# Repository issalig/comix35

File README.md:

# comix35
This repository contains projects for Comix35

## comixino
[SW and HW](https://github.com/issalig/comix35/tree/main/comixino) for loading (and saving in the future) data/programs without the need of another computer. It is basically a mix of the HSDC and TZXDuino.

### SW
Comixino [software](https://github.com/issalig/comix35/tree/main/comixino/sw) is basically and adaption of TZXDuino for the COMIX-35. However, communication is not cassette-based but serial is used.
By pressing up/down buttons it is possible to navigate through the file system. Then, pressing PLAY will transmit the file to the COMIX-35. Please remember to type "PLOAD" in the COMIX-35 before pressing PLAY.
Recording is done similarly. First press RECORD button on comixino, then type "PSAVE" in COMIX-35. However, "record" function does not work correctly as it misses some bytes. If you can help me, please do it.

It is possible to use hardware serial or software serial (comment/uncomment #define SW_SERIAL 1)

### HW
Comixino [board](https://github.com/issalig/comix35/tree/main/comixino/hw) is made up of an Arduino Uno, OLED screen, and SD card reader and connects to the expansion port. However, it just uses 3 connections /EF4, Q and GND.
A pass-trough connection is also available allowing to experiment with the bus signals.

## Keycaps
[Keycaps](https://github.com/issalig/comix35/tree/main/keycaps) for the Comix35 clone (https://github.com/schlae/comix-35)

## Case
Modified [case](https://github.com/issalig/comix35/tree/main/case) based in https://www.thingiverse.com/thing:5405097 with hole for cartridges and left aligned keys. Suitable for printing in small/standard 3d printers.

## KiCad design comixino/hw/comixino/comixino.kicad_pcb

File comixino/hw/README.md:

# COMIXINO - COMX File Player/Recorder

## Overview
COMIXINO is an Arduino-based project that plays and records COMX files using High Speed Direct Connection (HDSC). It's designed to work with the COMX-35 computer system, allowing you to transfer programs and data between a modern SD card storage and the vintage computer.

## Hardware configuration
There are some jumpers that need to be configured.
 - J1: Powers Arduino from COMX-35. If Comixino is connected to the PC through USB it would be better not to have the jumper but it is proven to work. (Necessary)
 - J2: If connected it resets both Comixino and COMX-35 when reset button is pressed. (Recommended)
 - J11: TX. Set to HW (hardware serial) as default option. Set it to SW (software serial) if you compiled it ```#define SW_SERIAL 1 ``` (Recommended HW)
- J12: RX. Set to HW (hardware serial) as default option. Set it to SW (software serial) if you compiled it ```#define SW_SERIAL 1 ``` (Recommended HW)
 - J8: Original connector from HSDC board that plugs to an RS232-USB converter.
 - J7: Exposed pins for software serial TX/RX (not necessary)

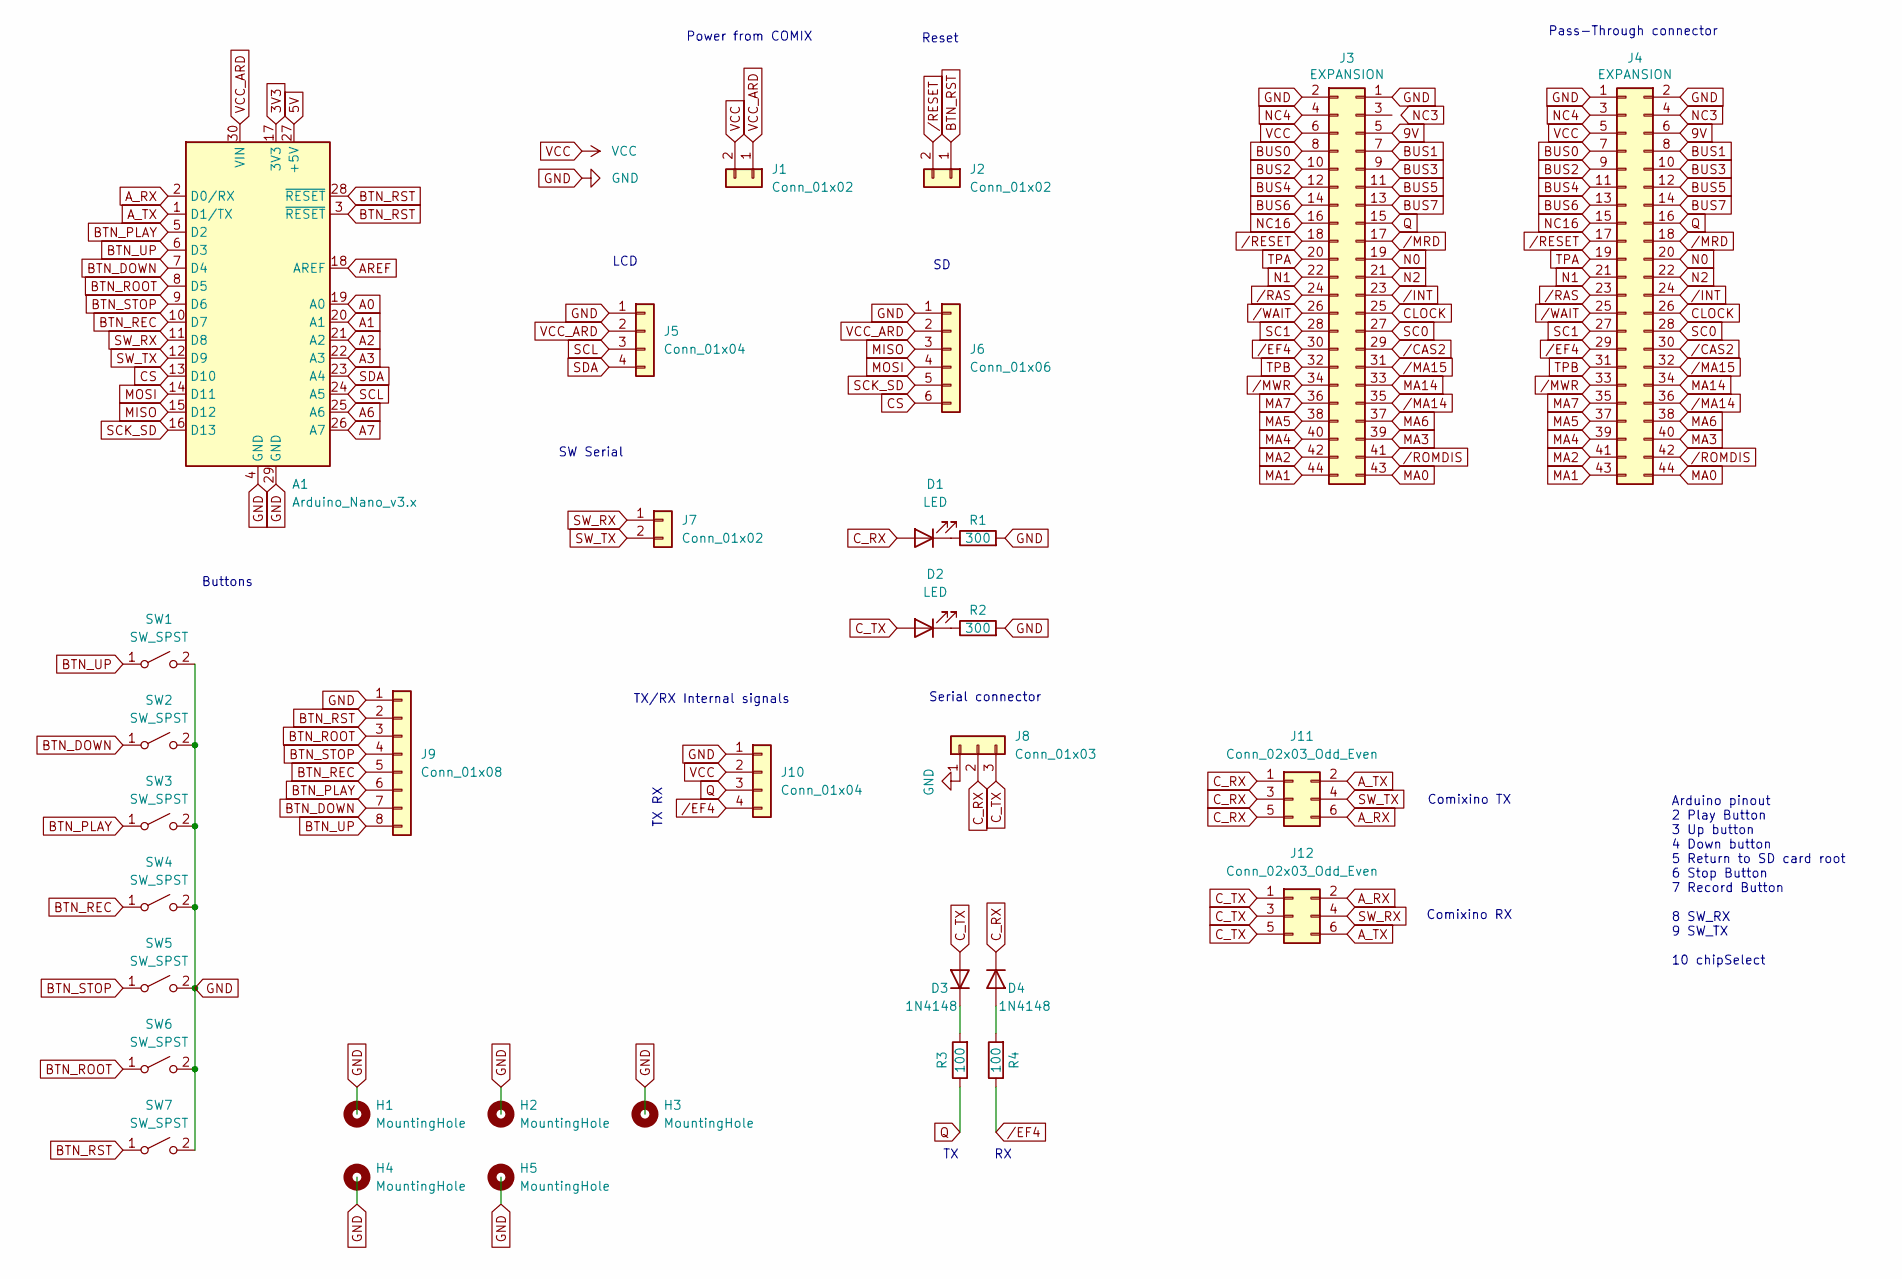
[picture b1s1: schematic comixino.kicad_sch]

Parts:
A1: Arduino_Nano_v3.x; Arduino_Nano_WithMountingHoles
D1, D2: LED; LED_D3.0mm
D3, D4: 1N4148; D_DO-35_SOD27_P7.62mm_Horizontal
H1, H2, H3, H4, H5: MountingHole; MountingHole_3.2mm_M3_DIN965_Pad
J1: Conn_01x02; PinHeader_1x02_P2.54mm_Horizontal
J2, J7: Conn_01x02; PinHeader_1x02_P2.54mm_Vertical
J3: EXPANSION; Edge_Card_Connector_22x2; Digikey S3316-ND
J4: EXPANSION; PinHeader_2x22_P2.54mm_Vertical; Digikey S3316-ND
J5, J10: Conn_01x04; PinHeader_1x04_P2.54mm_Vertical
J6: Conn_01x06; PinHeader_1x06_P2.54mm_Vertical
J8: Conn_01x03; PinHeader_1x03_P2.54mm_Horizontal
J9: Conn_01x08; PinHeader_1x08_P2.54mm_Vertical
J11, J12: Conn_02x03_Odd_Even; PinHeader_2x03_P2.54mm_Horizontal
R1, R2: 300; R_Axial_DIN0204_L3.6mm_D1.6mm_P7.62mm_Horizontal
R3, R4: 100; R_Axial_DIN0204_L3.6mm_D1.6mm_P7.62mm_Horizontal
SW1, SW2, SW3, SW4, SW5, SW6, SW7: SW_SPST; SW_PUSH_6mm_H5mm

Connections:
3V3: A1.17 (3V3)
5V: A1.27 (+5V)
9V: J3.5 (pin), J4.6
A0: A1.19 (A0)
A1: A1.20 (A1)
A2: A1.21 (A2)
A3: A1.22 (A3)
A6: A1.25 (A6)
A7: A1.26 (A7)
AREF: A1.18 (AREF)
A_RX: A1.2 (D0/RX), J11.6, J12.2
A_TX: A1.1 (D1/TX), J11.2, J12.6
BTN_DOWN: A1.7 (D4), J9.7, SW2.1 (A)
BTN_PLAY: A1.5 (D2), J9.6, SW3.1 (A)
BTN_REC: A1.10 (D7), J9.5, SW4.1 (A)
BTN_ROOT: A1.8 (D5), J9.3, SW6.1 (A)
BTN_RST: A1.3 (~RESET), A1.28 (~RESET), J2.1, J9.2, SW7.1 (A)
BTN_STOP: A1.9 (D6), J9.4, SW5.1 (A)
BTN_UP: A1.6 (D3), J9.8, SW1.1 (A)
BUS0: J3.8, J4.7 (pin)
BUS1: J3.7 (pin), J4.8
BUS2: J3.10, J4.9 (pin)
BUS3: J3.9 (pin), J4.10
BUS4: J3.12, J4.11 (pin)
BUS5: J3.11 (pin), J4.12
BUS6: J3.14, J4.13 (pin)
BUS7: J3.13 (pin), J4.14
CLOCK: J3.25 (pin), J4.26
CS: A1.13 (D10), J6.6
C_RX: D1.2 (A), D4.1 (K), J8.2, J11.1, J11.3, J11.5
C_TX: D2.2 (A), D3.2 (A), J8.3, J12.1, J12.3, J12.5
GND: A1.4 (GND), A1.29 (GND), J3.1 (pin), J3.2, J4.1 (pin), J4.2, J5.1, J6.1, J8.1, J9.1, J10.1, R1.2, R2.2, SW1.2 (B), SW2.2 (B), SW3.2 (B), SW4.2 (B), SW5.2 (B), SW6.2 (B), SW7.2 (B)
MA0: J3.43 (pin), J4.44
MA1: J3.44, J4.43 (pin)
MA2: J3.42, J4.41 (pin)
MA3: J3.39 (pin), J4.40
MA4: J3.40, J4.39 (pin)
MA5: J3.38, J4.37 (pin)
MA6: J3.37 (pin), J4.38
MA7: J3.36, J4.35 (pin)
MA14: J3.33 (pin), J4.34
MISO: A1.15 (D12), J6.3
MOSI: A1.14 (D11), J6.4
N0: J3.19 (pin), J4.20
N1: J3.22, J4.21 (pin)
N2: J3.21 (pin), J4.22
NC3: J4.4
NC4: J3.4, J4.3 (pin)
NC16: J3.16, J4.15 (pin)
unnamed: D1.1 (K), R1.1
unnamed: D2.1 (K), R2.1
unnamed: D3.1 (K), R3.2
unnamed: D4.2 (A), R4.2
Q: J3.15 (pin), J4.16, J10.3, R3.1
SC0: J3.27 (pin), J4.28
SC1: J3.28, J4.27 (pin)
SCK_SD: A1.16 (D13), J6.5
SCL: A1.24 (A5), J5.3
SDA: A1.23 (A4), J5.4
SW_RX: A1.11 (D8), J7.1, J12.4
SW_TX: A1.12 (D9), J7.2, J11.4
TPA: J3.20, J4.19 (pin)
TPB: J3.32, J4.31 (pin)
VCC: J1.2, J3.6, J4.5 (pin), J10.2
VCC_ARD: A1.30 (VIN), J1.1, J5.2, J6.2
/CAS2: J3.29 (pin), J4.30
/EF4: J3.30, J4.29 (pin), J10.4, R4.1
/INT: J3.23 (pin), J4.24
/MA14: J3.35 (pin), J4.36
/MA15: J3.31 (pin), J4.32
/MRD: J3.17 (pin), J4.18
/MWR: J3.34, J4.33 (pin)
/RAS: J3.24, J4.23 (pin)
/RESET: J2.2, J3.18, J4.17 (pin)
/ROMDIS: J3.41 (pin), J4.42
/WAIT: J3.26, J4.25 (pin)

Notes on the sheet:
Arduino pinout 2 Play Button 3 Up button 4 Down button 5 Return to SD card root 6 Stop Button 7 Record Button 8 SW_RX 9 SW_TX 10 chipSelect
Comixino TX
Serial connector
TX/RX Internal signals
Power from COMIX
Buttons
LCD
Comixino RX
Pass-Through connector
Reset
SW Serial

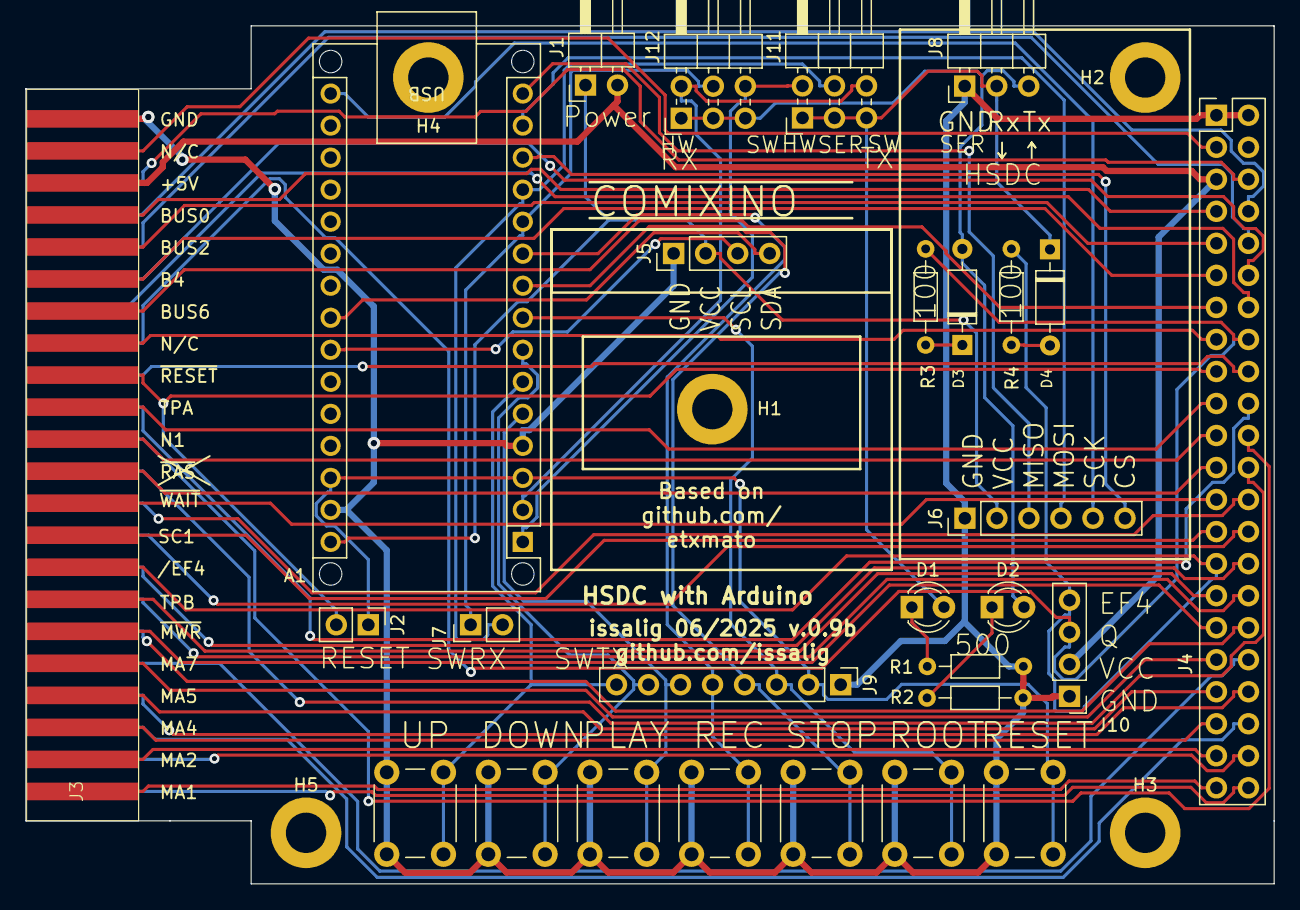
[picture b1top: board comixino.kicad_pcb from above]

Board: 2 copper layers, 99.0 x 68.0 mm, 33 parts (0 on the bottom side), 66 nets.

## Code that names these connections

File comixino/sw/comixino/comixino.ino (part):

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
#ifdef SW_SERIAL
// pins for rx/tx software serial
#define SW_RX 8
#define SW_TX 9
SoftwareSerial sw_serial(SW_RX, SW_TX, false); // RX, TX
//AltSoftSerial  sw_serial;
//NeoSWSerial sw_serial(SW_RX, SW_TX);
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// Pin definitions
#define SD_CS     10                 // Sd card chip select pin

#define BTN_UP     3                 // Up button 
#define BTN_DOWN   4                 // Down button
#define BTN_PLAY   2                 // Play Button
#define BTN_STOP   6                 // Stop Button
#define BTN_ROOT   5                 // Return to SD card root
#define BTN_RECORD 7                 // Record Button


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    show_splashscreen();        

    #ifdef SW_SERIAL
    pinMode(SW_RX, INPUT_PULLUP);
    pinMode(SW_TX, OUTPUT);
    sw_serial.begin(baudrates[baudrate_index]); // Set the baud rate for sw_serial
    #endif 
    
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    is_stopped = true;
  
    // General Pin settings
    pinMode(BTN_PLAY, INPUT_PULLUP);
    digitalWrite(BTN_PLAY, HIGH);

    pinMode(BTN_STOP, INPUT_PULLUP);
    digitalWrite(BTN_STOP, HIGH);
    
    pinMode(BTN_UP, INPUT_PULLUP);
    digitalWrite(BTN_UP, HIGH);
    
    pinMode(BTN_DOWN, INPUT_PULLUP);
    digitalWrite(BTN_DOWN, HIGH);
    
    pinMode(BTN_RECORD, INPUT_PULLUP);
    digitalWrite(BTN_RECORD, HIGH);
    
    pinMode(BTN_ROOT, INPUT_PULLUP);
    digitalWrite(BTN_ROOT, HIGH);

    get_max_file();                     // get the total number of files in the directory
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
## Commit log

2025-06-14 comixino
2025-06-14 keycaps
2025-06-15 hw and case
2025-06-15 case
2025-06-16 photo
2025-06-30 fixed record function
2025-06-30 readme
2025-06-30 clean
2025-07-01 kicad
